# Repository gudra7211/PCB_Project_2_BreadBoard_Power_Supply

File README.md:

# PCB_Project_2_BreadBoard_Power_Supply
This KiCAD-designed PCB seamlessly integrates into breadboard rails, providing a convenient and efficient power source. Featuring dual voltage options of 5V and 3.3V, easily selectable through onboard switches, this PCB empowers rapid prototyping and experimentation. Its streamlined design and direct breadboard compatibility enhance workspace organization and accelerate project development.

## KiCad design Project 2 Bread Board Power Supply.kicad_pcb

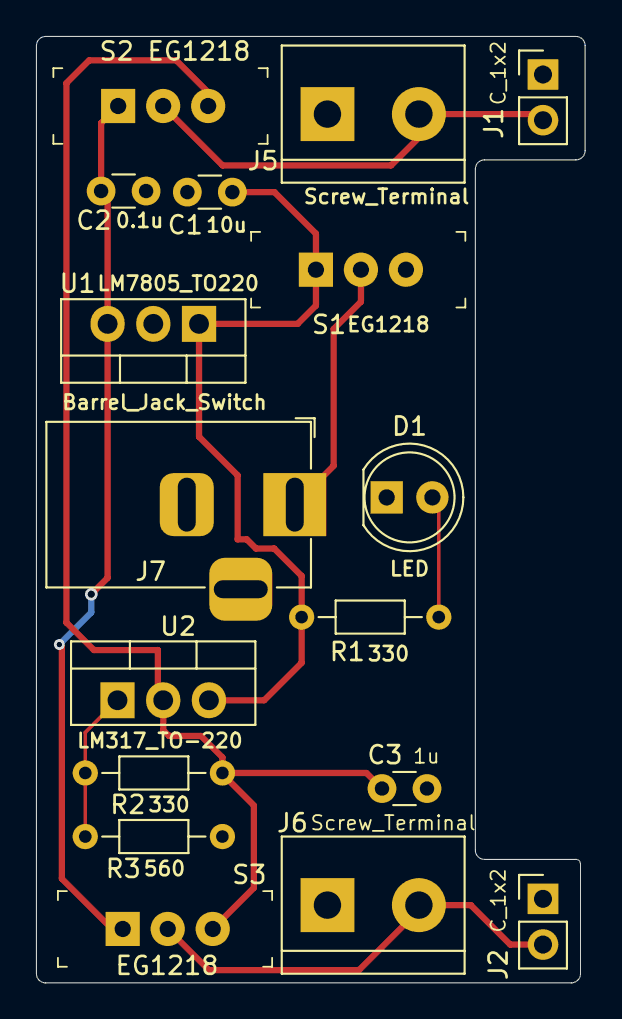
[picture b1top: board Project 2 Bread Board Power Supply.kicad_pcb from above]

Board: 2 copper layers, 30.5 x 52.6 mm, 17 parts (0 on the bottom side), 9 nets.

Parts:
C1: 10u; C_Disc_D3.0mm_W1.6mm_P2.50mm
C2: 0.1u; C_Disc_D3.0mm_W1.6mm_P2.50mm
C3: 1u; C_Disc_D3.0mm_W1.6mm_P2.50mm
D1: LED; LED_D5.0mm
J1, J2: C_1x2; PinHeader_1x02_P2.54mm_Vertical
J5, J6: Screw_Terminal; TerminalBlock_bornier-2_P5.08mm
J7: Barrel_Jack_Switch; BarrelJack_Horizontal
R1, R2: 330; R_Axial_DIN0204_L3.6mm_D1.6mm_P7.62mm_Horizontal
R3: 560; R_Axial_DIN0204_L3.6mm_D1.6mm_P7.62mm_Horizontal
S1, S2, S3: EG1218; Switch_Slide_11.6x4mm_EG1218
U1: LM7805_TO220; TO-220-3_Vertical
U2: LM317_TO-220; TO-220-3_Vertical

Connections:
/3.3V: C3.1, R2.2, S2.3, S3.3, U2.2 (VO)
/5V: C2.1, S2.1, S3.1, U1.3 (VO)
/12V: C1.1, R1.2, S1.1, U1.1 (VI), U2.3 (VI)
/Power_Op_Bottom: J2.2, J6.2, S3.2
/Power_Op_Top: J1.2, J5.2, S2.2
/Power_ip: J7.1, S1.2
GND: C1.2, C2.2, C3.2, D1.1 (K), J1.1, J2.1, J5.1, J6.1, J7.2, J7.3, R3.1, U1.2 (GND)
unnamed: D1.2 (A), R1.1
unnamed: R2.1, R3.2, U2.1 (ADJ)
